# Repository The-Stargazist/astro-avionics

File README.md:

# Astro Avionics: VADA Flight Computer

Dual-computer avionics for amateur and student rockets. The **VADA** board
carries two Raspberry Pi Pico 2 microcontrollers that fly independently:

- **Pico A** watches its own barometer and deploys the parachute.
- **Pico B** reads every sensor and the GPS, sends live LoRa telemetry and
  keeps a detailed log.

Each computer has its own barometer, I2C bus and SD card, so a failure on one
does not take down the other.

> [!WARNING]
> This system controls pyrotechnic charges. The firmware has been rebuilt and
> tested in simulation, but **has not yet flown or been bench-tested on the
> VADA board**. Read [Known issues](#known-issues) and bench-test every pyro
> channel before any flight.

---

## Contents

- [How it works](#how-it-works)
- [Hardware](#hardware)
- [Flight sequence](#flight-sequence)
- [Getting started](#getting-started)
- [Pre-flight checklist](#pre-flight-checklist)
- [Flight data](#flight-data)
- [Repository layout](#repository-layout)
- [Known issues](#known-issues)
- [History](#history)
- [Credits and license](#credits-and-license)

---

## How it works

```mermaid
flowchart LR
    subgraph railA["I2C rail A"]
        IMU["ICM-20649 IMU"]
        MAG["LIS3MDL magnetometer"]
        BMPA["BMP390 A"]
    end
    subgraph railB["I2C rail B"]
        BMPB["BMP390 B"]
    end

    PB["Pico B: sensors, telemetry, logging (FreeRTOS)"]
    PA["Pico A: deployment (dual core)"]

    railA -- "JP1/JP2" --> PB
    railB -- "JP3/JP4" --> PA
    GPS["u-blox M8N GPS"] -- UART --> PB
    PB -- SPI --> LORA["RA-02 LoRa 433 MHz"]
    PB -- SPI --> SDB["SD card B"]
    PA -- SPI --> SDA["SD card A"]
    PA -- fires --> MAIN["MAIN charge"]
    PA -- fires --> BACKUP["BACKUP charge"]
    PB -. "continuity check" .-> MAIN
    PB -. "continuity check" .-> BACKUP
```

| | Pico A: deployment | Pico B: sensors and telemetry |
|---|---|---|
| Barometer | BMP390 "B" (rail B) | BMP390 "A" (rail A) |
| Other sensors | — | ICM-20649 IMU, LIS3MDL magnetometer, GPS |
| Fires pyro charges | **Yes**: MAIN at apogee, BACKUP on overspeed | No (outputs held low) |
| Continuity checks | MAIN, BACKUP, MOTOR, STAGE, check loop | MAIN, BACKUP |
| Logging | SD card A, 50 Hz, `flightNNN.csv` | SD card B, 50 Hz, `telemNNN.csv` |
| Telemetry | — | LoRa, 4 packets/s |
| Runtime | Core 0 flies, core 1 writes the SD card | FreeRTOS tasks |

Both boards run the same flight-phase logic on their own barometer. Pico A
acts on it; Pico B reports it in its log and telemetry. Neither board ever
waits on the SD card or USB while making flight decisions.

## Hardware

The KiCad project for the VADA PCB is in [`vada/`](vada). Everything below
was read from `vada/VADA.kicad_pcb`.

| Part | Function | Connected to |
|------|----------|--------------|
| 2 × Raspberry Pi Pico 2 (RP2350) | Flight computers A and B | — |
| 2 × BMP390 | Barometric altitude | One per I2C rail |
| ICM-20649 | 6-axis IMU, ±30 g / ±2000 °/s | Rail A (Pico B) |
| LIS3MDL | 3-axis magnetometer | Rail A (Pico B) |
| u-blox M8N | GPS | Pico B UART1 (GPIO8/9) |
| Ai-Thinker RA-02 (SX1278) | 433 MHz LoRa radio | Pico B SPI0 |
| 2 × microSD socket | Data logging | One per Pico, SPI0 |
| 4 × CPC1020N solid-state relay | Pyro channels | See below |
| NCP1117-3.3 | 3.3 V regulator from the 5 V input (J1) | — |

**Pyro channels.** Each channel has three lines: TRIG switches battery
power (J7) to the e-match, CONT sends a tiny test current through it, and
SENSE reads it back.

| Channel | Connector | Wired to | Firmware use |
|---------|-----------|----------|--------------|
| MAIN | J2 "Pyro 3" | Both Picos (diode-OR) | Fired by Pico A at apogee |
| BACKUP | J3 "Pyro 4" | Both Picos (diode-OR) | Fired by Pico A if descending too fast |
| MOTOR | J5 "Pyro 1" | Pico A only | Held off, continuity reported |
| STAGE | J6 "Pyro 2" | Pico A only | Held off, continuity reported |

The full pin map for both boards is in
[`firmware/lib/board/VadaPins.h`](firmware/lib/board/VadaPins.h).

## Flight sequence

```mermaid
stateDiagram-v2
    [*] --> GROUND: power on, 1 s ground reference
    GROUND --> FLIGHT: above 200 m AGL for 100 ms
    FLIGHT --> DESCENT: apogee, velocity below 2 m/s for 100 ms, fire MAIN
    DESCENT --> DESCENT: falling faster than 20 m/s for 200 ms, fire BACKUP once
    DESCENT --> LANDED: speed below 2 m/s for 20 s, close log
```

1. **Ground reference.** At power-on each board takes the median of 1 s of
   barometer readings as "pad altitude". All altitudes after that are above
   ground level (AGL).
2. **Filtering.** Raw barometer readings are noisy. A filter smooths them
   into altitude and vertical speed, and throws away single readings that
   are more than 50 m off (a corrupted sensor read).
3. **Launch.** Above 200 m AGL the board switches to FLIGHT. While on the
   ground, Pico A re-checks continuity every second.
4. **Apogee.** When the rocket stops climbing, Pico A fires MAIN for 500 ms.
5. **Overspeed.** If the rocket then falls faster than 20 m/s (main
   failed), Pico A fires BACKUP for 1 s and then MAIN again. This check is
   ignored for the first 2 s after apogee, because the ejection charge
   briefly upsets the barometer.
6. **Landing.** After 20 s with almost no vertical movement, Pico A closes
   its log file.

Every transition has to hold over time, so one bad reading can't trigger it.
All thresholds are in `FlightConfig` in
[`firmware/lib/flight/FlightComputer.h`](firmware/lib/flight/FlightComputer.h).

## Getting started

### Prerequisites

- [PlatformIO](https://platformio.org): either the VS Code extension or the
  command line (`pip install platformio`)
- `gcc` and `g++` on your `PATH` to run the unit tests (on Windows, MSYS2
  or MinGW)

### Build

```bash
git clone https://github.com/The-Stargazist/astro-avionics.git
```

```bash
cd astro-avionics/firmware
```

```bash
pio run
```

The first build downloads the RP2350 toolchain, which takes a few minutes.

### Flash

Connect one Pico at a time over USB. If the upload can't find the board,
unplug it, hold the **BOOTSEL** button and plug it back in.

```bash
pio run -e pico_a -t upload
```

```bash
pio run -e pico_b -t upload
```

Watch the output over USB (Pico A prints its log, Pico B prints a status line
every second):

```bash
pio device monitor
```

### Test

```bash
pio test -e native
```

This runs 22 tests on your computer, no hardware needed:

- simulated flights: normal, failed main, sensor glitches
- GPS sentence parsing
- barometer maths against Bosch's reference values

GitHub Actions runs the tests and both builds on every push.

### Board setup

**Bridge all four solder jumpers JP1, JP2, JP3 and JP4.** They connect
rail A to Pico B and rail B to Pico A. Without them neither board can see its
barometer.

## Pre-flight checklist

1. JP1–JP4 bridged. Two FAT32-formatted microSD cards inserted.
2. Power on **at the launch site**. The pad altitude is measured in the
   first second, so powering on somewhere else shifts every altitude.
3. Check both status LEDs:

   | LED | Meaning |
   |-----|---------|
   | 1 Hz blink | Ready |
   | Solid | MAIN or BACKUP e-match not detected |
   | 5 Hz blink | Sensor, SD card or (Pico B) radio fault |

4. Confirm telemetry is arriving. The `flags` field should show barometer,
   IMU, magnetometer, SD and radio OK, MAIN and BACKUP continuity, and a GPS
   fix (needed for recovery).
5. Check the e-matches are connected before final arming. Pico A re-checks
   continuity every second until launch.

## Flight data

| | Pico A | Pico B |
|---|---|---|
| File | `flightNNN.csv` | `telemNNN.csv` |
| Rate | 50 Hz | 50 Hz |
| Columns | time, pressure, temperature, raw and filtered altitude, velocity, phase | All of Pico A's, plus IMU, magnetometer, GPS and health flags |

A new file is created at every power-on, and data is flushed to the card ten
times a second. Lines starting with `#` are events (launch, apogee, faults);
load the files with `pandas.read_csv(path, comment="#")`.

**Telemetry** (Pico B, LoRa 433 MHz, SF7) is one plain-text line per packet:

```
VADA,time_ms,phase,alt_m,vel_mps,max_alt_m,lat,lon,sats,flags
```

The column definitions and the `flags` bits are in
[`firmware/README.md`](firmware/README.md).

## Repository layout

```
firmware/              current flight software (PlatformIO project)
  src/pico_a/          Pico A application
  src/pico_b/          Pico B application
  lib/board/           pin map for both boards
  lib/flight/          filter, ground reference, flight phases (pure C++, unit-tested)
  lib/gps/             NMEA GPS parser (pure C++, unit-tested)
  lib/sensors/         BMP390, ICM-20649, LIS3MDL drivers
  lib/pyro/            continuity test and firing
  lib/logging/         non-blocking log buffer, SD file naming
  test/                host unit tests
  tools/               MicroPython bring-up script for Pico B
vada/                  VADA PCB: KiCad schematic, layout, 3D model
dosa-2025/             previous flight computer (archived)
```

Technical detail for developers (task layout, file formats, tuning) is in
[`firmware/README.md`](firmware/README.md).

## Known issues

- **Pyro drive current may be too low (hardware).** By the resistor values
  in the PCB file, each solid-state relay gets only about 10–40 µA to switch
  on, but the CPC1020N needs milliamps. If those values are what's fitted,
  the charges may never fire. Bench-test every channel with an e-match
  substitute.
- **No hardware test yet.** The rebuilt firmware compiles and passes its
  simulations, but has not run on a VADA board.
- **Pico A relies on one barometer.** If it fails mid-flight there is no
  timer-based fallback deployment.
- **Only Pico A fires.** The hardware lets Pico B fire MAIN and BACKUP too,
  as a redundant second deployment computer. The firmware doesn't use that.
- **Pico-to-Pico link unused.** The boards are connected by a UART (GPIO0/1)
  that the firmware does not use yet.
- **Barometer labels.** In the schematic the barometers are labelled
  BMP585, but the footprints and firmware are for the BMP390.

## History

- **2025: DOSA** ([`dosa-2025/`](dosa-2025)). Arduino Nano ESP32 for flight
  control plus a Raspberry Pi for logging, camera and backup deployment.
  Archived for reference, not maintained.
- **VADA.** Custom dual-Pico PCB. Separate Pico A and Pico B projects were
  merged into one tested firmware project in `firmware/`.

## Credits and license

This project uses code from Astro Avionics Flight Computer. This fork
(The-Stargazist/astro-avionics) is based on
[YogPanjarale/astro-avionics](https://github.com/YogPanjarale/astro-avionics)
and its contributors.

Released under the MIT License with an attribution requirement: if you use,
modify or distribute this code, credit the original authors. See
[`LICENSE`](LICENSE) for the full terms.

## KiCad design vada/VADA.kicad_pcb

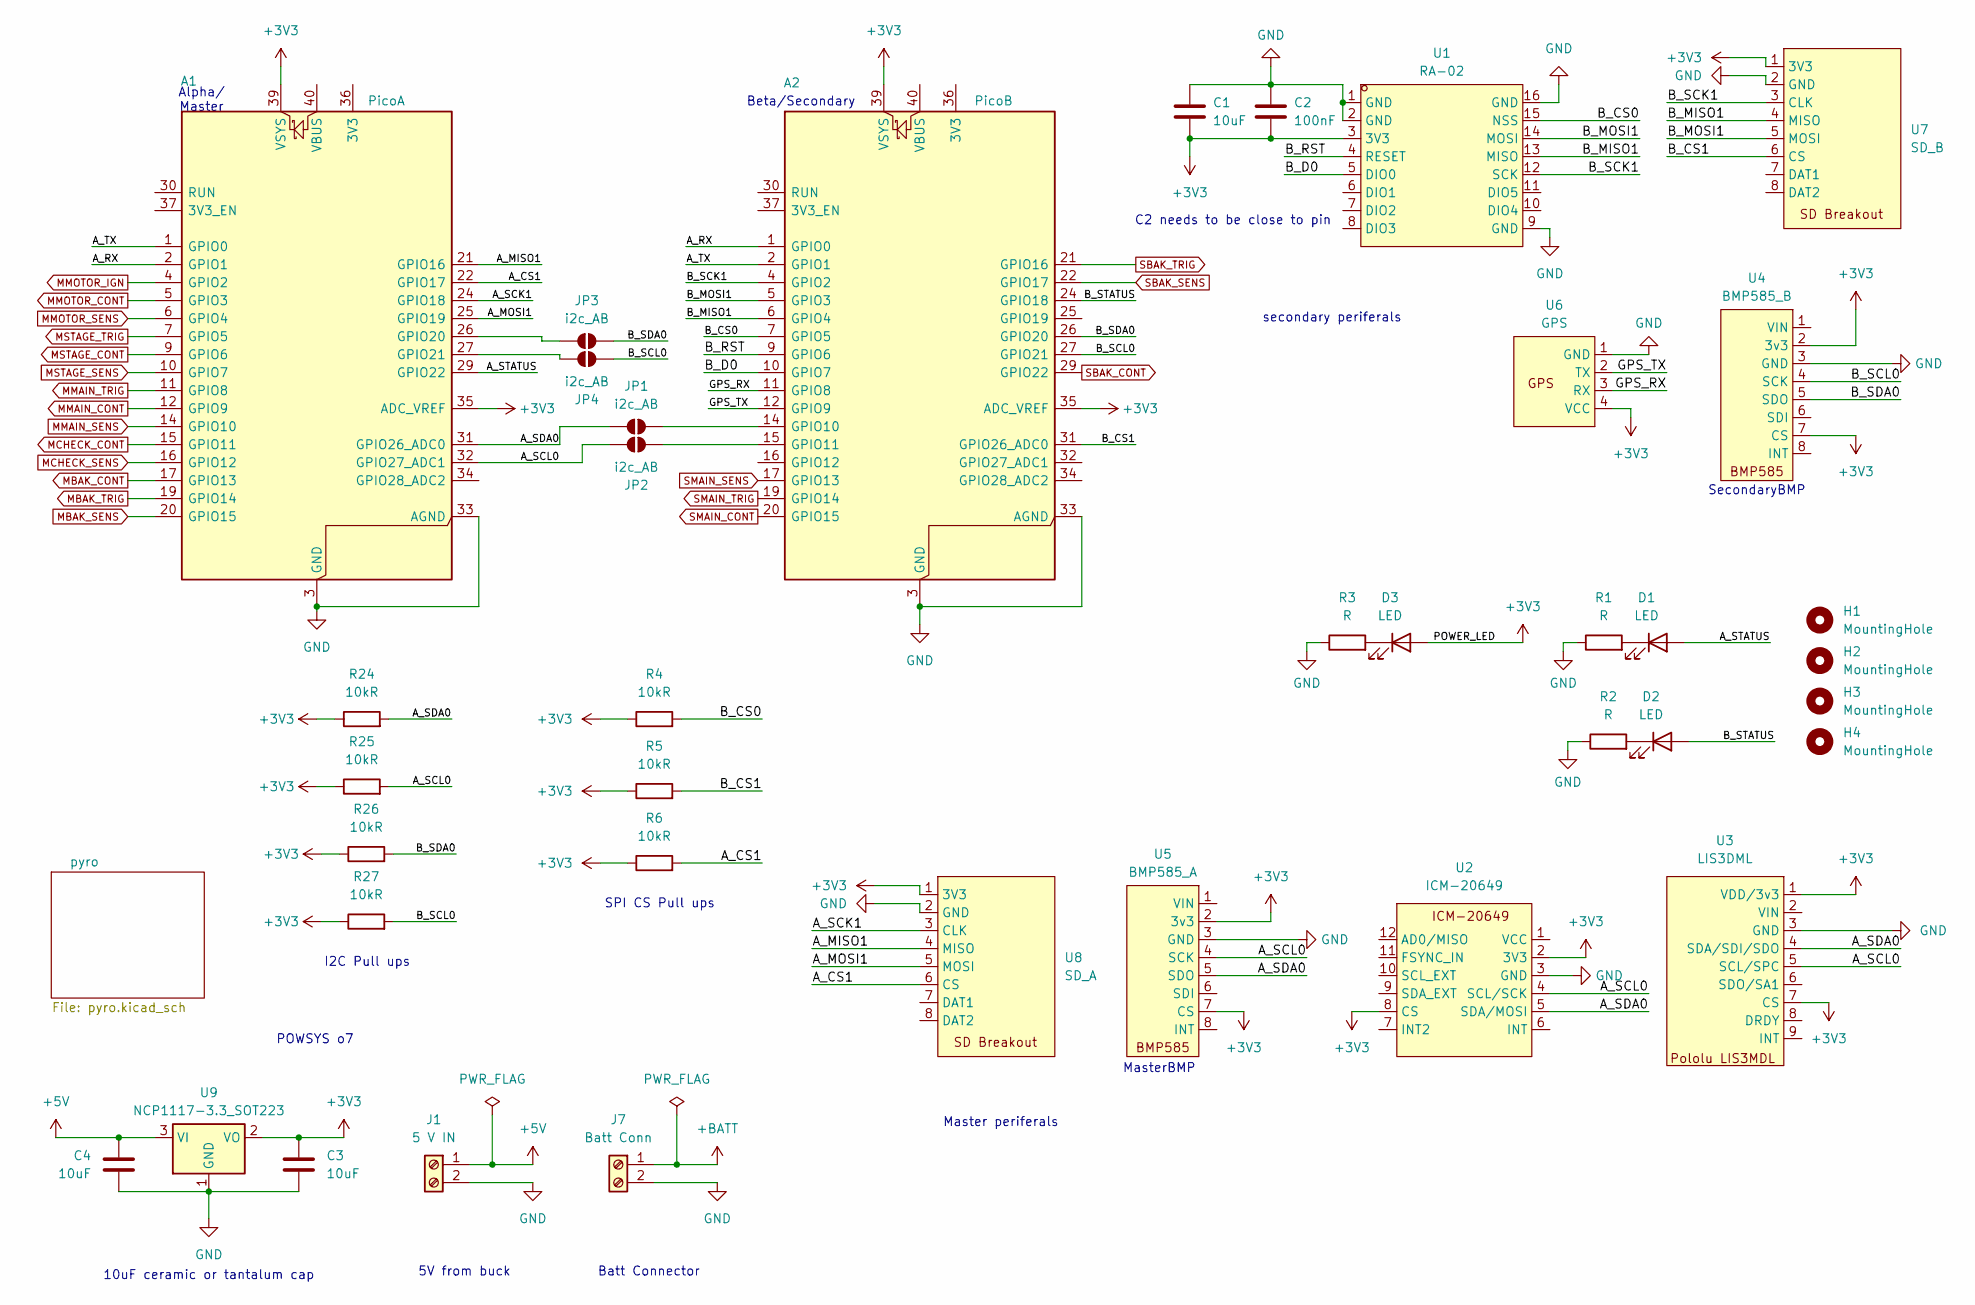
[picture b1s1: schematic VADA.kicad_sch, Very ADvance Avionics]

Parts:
A1: PicoA; RaspberryPi_Pico_Common_THT
A2: PicoB; RaspberryPi_Pico_Common_THT
C1, C3, C4: 10uF; C_1206_3216Metric_Pad1.33x1.80mm_HandSolder
C2: 100nF; C_1206_3216Metric_Pad1.33x1.80mm_HandSolder
D1, D2, D3: LED; LED_D3.0mm
H1, H2, H3, H4: MountingHole; MountingHole_3.2mm_M3
J1: 5 V IN; TerminalBlock_Phoenix_MKDS-1,5-2_1x02_P5.00mm_Horizontal
J7: Batt Conn; TerminalBlock_Phoenix_MKDS-1,5-2_1x02_P5.00mm_Horizontal
JP1, JP2, JP3, JP4: i2c_AB; SolderJumper-2_P1.3mm_Open_Pad1.0x1.5mm
R1, R2, R3: R; R_Axial_DIN0207_L6.3mm_D2.5mm_P7.62mm_Horizontal
R4, R5, R6, R24, R25, R26, R27: 10kR; R_0805_2012Metric_Pad1.20x1.40mm_HandSolder
U1: RA-02; WIRELM-SMD_RA-02-BL; LCSC Part C90039
U2: ICM-20649
U3: LIS3DML; Pololu LIS3DML
U4: BMP585_B; BMP-390L
U5: BMP585_A; BMP-390L
U6: GPS; M8N GPS
U7: SD_B; PinSocket_1x08_P2.54mm_Vertical
U8: SD_A; PinSocket_1x08_P2.54mm_Vertical
U9: NCP1117-3.3_SOT223; SOT-223-3_TabPin2

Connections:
+3V3: A1.35 (ADC_VREF), A1.39 (VSYS), A2.35 (ADC_VREF), A2.39 (VSYS), C1.2, C2.2, C3.1, D3.2 (A), R4.1, R5.1, R6.1, R24.1, R25.1, R26.1, R27.1, U1.3 (3V3), U2.2 (3V3), U2.8 (CS), U3.1 (VDD/3v3), U3.7 (CS), U4.2 (3v3), U4.7 (CS), U5.2 (3v3), U5.7 (CS), U6.4 (VCC), U7.1 (3V3), U8.1 (3V3), U9.2 (VO)
+5V: C4.1, J1.1, U9.3 (VI)
+BATT: J7.1; also elsewhere on the board
/A_CS1: A1.22 (GPIO17), R6.2, U8.6 (CS)
/A_MISO1: A1.21 (GPIO16), U8.4 (MISO)
/A_MOSI1: A1.25 (GPIO19), U8.5 (MOSI)
/A_RX: A1.2 (GPIO1), A2.1 (GPIO0)
/A_SCK1: A1.24 (GPIO18), U8.3 (CLK)
/A_SCL0: A1.32 (GPIO27_ADC1), JP2.1 (A), R25.2, U2.4 (SCL/SCK), U3.5 (SCL/SPC), U5.4 (SCK)
/A_SDA0: A1.31 (GPIO26_ADC0), JP1.1 (A), R24.2, U2.5 (SDA/MOSI), U3.4 (SDA/SDI/SDO), U5.5 (SDO)
/A_STATUS: A1.29 (GPIO22), D1.2 (A)
/A_TX: A1.1 (GPIO0), A2.2 (GPIO1)
/B_CS0: A2.7 (GPIO5), R4.2, U1.15 (NSS)
/B_CS1: A2.31 (GPIO26_ADC0), R5.2, U7.6 (CS)
/B_D0: A2.10 (GPIO7), U1.5 (DIO0)
/B_MISO1: A2.6 (GPIO4), U1.13 (MISO), U7.4 (MISO)
/B_MOSI1: A2.5 (GPIO3), U1.14 (MOSI), U7.5 (MOSI)
/B_RST: A2.9 (GPIO6), U1.4 (RESET)
/B_SCK1: A2.4 (GPIO2), U1.12 (SCK), U7.3 (CLK)
/B_SCL0: A2.27 (GPIO21), JP4.2 (B), R27.2, U4.4 (SCK)
/B_SDA0: A2.26 (GPIO20), JP3.2 (B), R26.2, U4.5 (SDO)
/B_STATUS: A2.24 (GPIO18), D2.2 (A)
/GPS_RX: A2.11 (GPIO8), U6.3 (RX)
/GPS_TX: A2.12 (GPIO9), U6.2 (TX)
GND: A1.3 (GND), A1.8 (GND), A1.13 (GND), A1.18 (GND), A1.23 (GND), A1.28 (GND), A1.33 (AGND), A1.38 (GND), A2.3 (GND), A2.8 (GND), A2.13 (GND), A2.18 (GND), A2.23 (GND), A2.28 (GND), A2.33 (AGND), A2.38 (GND), C1.1, C2.1, C3.2, C4.2, J1.2, J7.2, R1.1, R2.1, R3.1, U1.1 (GND), U1.2 (GND), U1.9 (GND), U1.16 (GND), U2.3 (GND), U3.3 (GND), U4.3 (GND), U5.3 (GND), U6.1 (GND), U7.2 (GND), U8.2 (GND), U9.1 (GND); also elsewhere on the board
MBAK_CONT: A1.17 (GPIO13); also elsewhere on the board
MBAK_SENS: A1.20 (GPIO15), A2.22 (GPIO17); also elsewhere on the board
MBAK_TRIG: A1.19 (GPIO14); also elsewhere on the board
MCHECK_CONT: A1.15 (GPIO11); also elsewhere on the board
MCHECK_SENS: A1.16 (GPIO12); also elsewhere on the board
MMAIN_CONT: A1.12 (GPIO9); also elsewhere on the board
MMAIN_SENS: A1.14 (GPIO10), A2.17 (GPIO13); also elsewhere on the board
MMAIN_TRIG: A1.11 (GPIO8); also elsewhere on the board
MMOTOR_CONT: A1.5 (GPIO3); also elsewhere on the board
MMOTOR_IGN: A1.4 (GPIO2); also elsewhere on the board
MMOTOR_SENS: A1.6 (GPIO4); also elsewhere on the board
MSTAGE_CONT: A1.9 (GPIO6); also elsewhere on the board
MSTAGE_SENS: A1.10 (GPIO7); also elsewhere on the board
MSTAGE_TRIG: A1.7 (GPIO5); also elsewhere on the board
unnamed: A1.26 (GPIO20), JP3.1 (A)
unnamed: A1.27 (GPIO21), JP4.1 (A)
unnamed: A2.14 (GPIO10), JP1.2 (B)
unnamed: A2.15 (GPIO11), JP2.2 (B)
unnamed: D1.1 (K), R1.2
unnamed: D2.1 (K), R2.2
unnamed: D3.1 (K), R3.2
SBAK_CONT: A2.29 (GPIO22); also elsewhere on the board
SBAK_TRIG: A2.21 (GPIO16); also elsewhere on the board
SMAIN_CONT: A2.20 (GPIO15); also elsewhere on the board
SMAIN_TRIG: A2.19 (GPIO14); also elsewhere on the board

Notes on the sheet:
10uF ceramic or tantalum cap
5V from buck
C2 needs to be close to pin
Batt Connector
SPI CS Pull ups
MasterBMP
Alpha/ Master
Master periferals
POWSYS o7
I2C Pull ups
secondary periferals
SecondaryBMP
Beta/Secondary

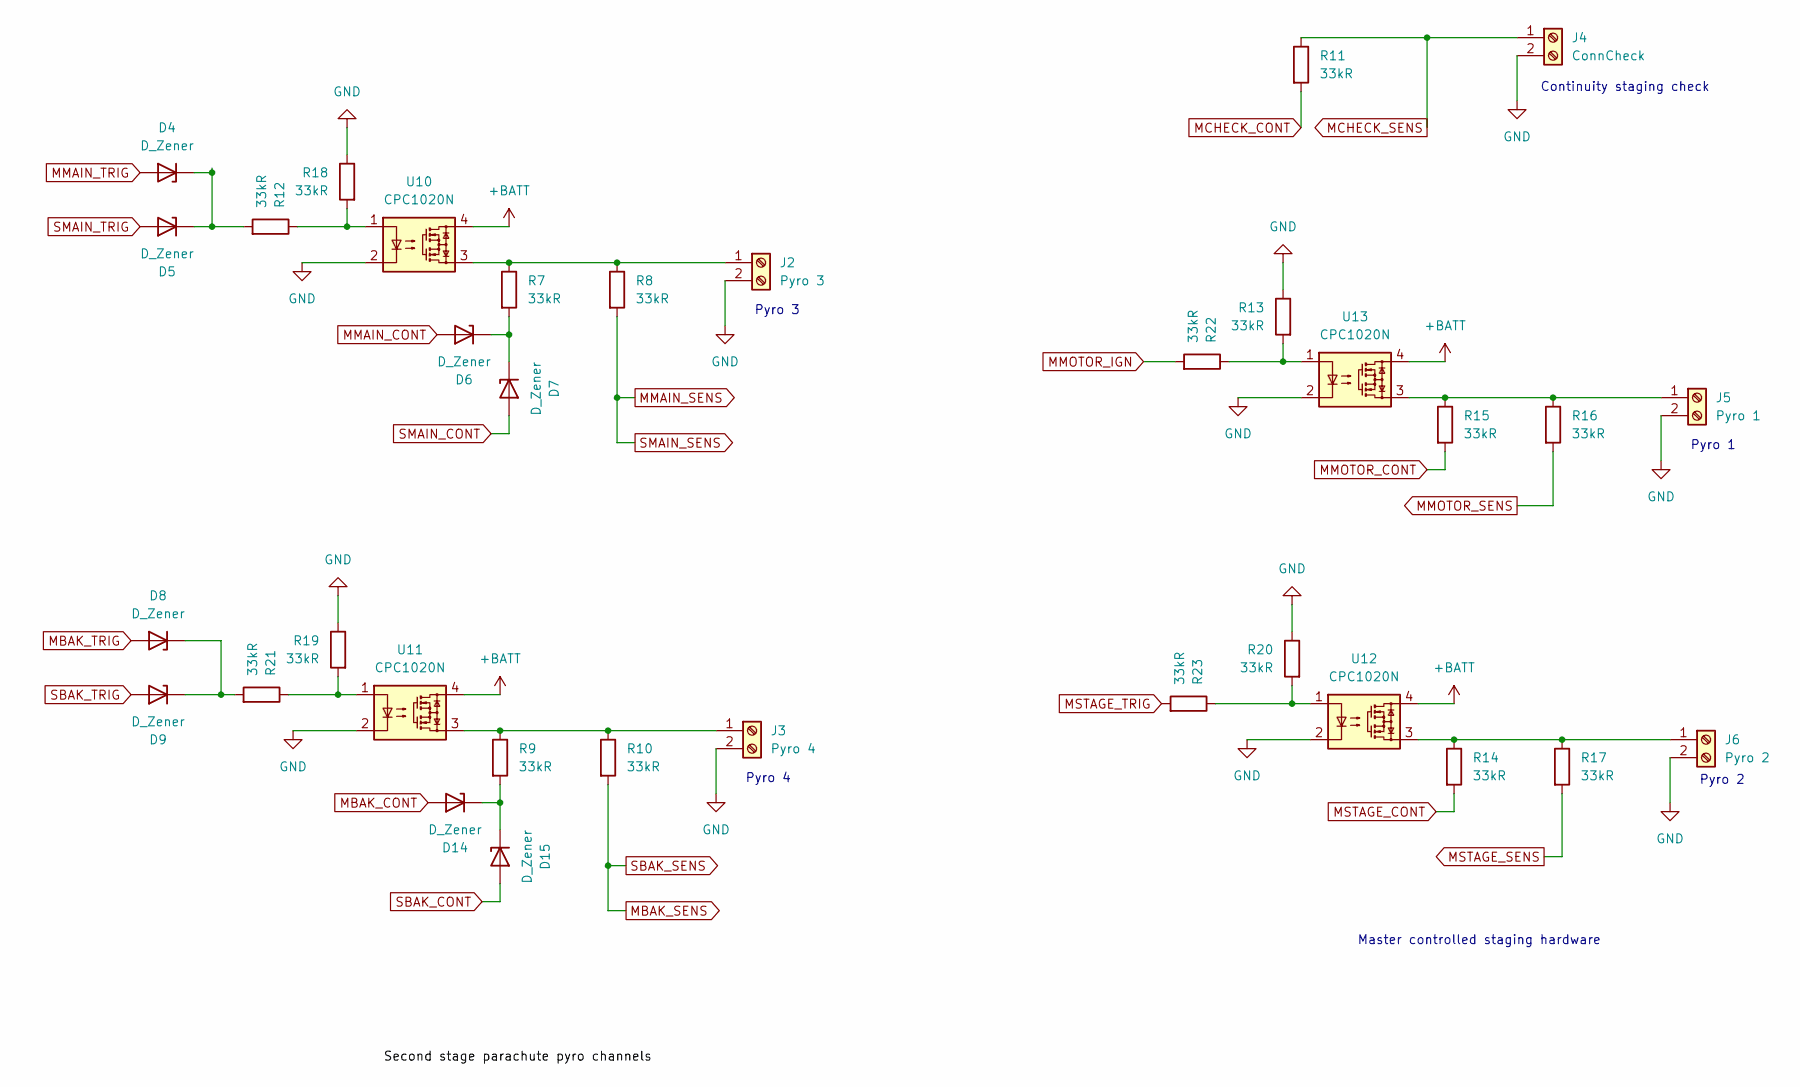
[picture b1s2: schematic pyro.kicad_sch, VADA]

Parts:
D4, D5, D6, D7, D8, D9, D14, D15: D_Zener; D_SOD-123F
J2: Pyro 3; TerminalBlock_Phoenix_MKDS-1,5-2_1x02_P5.00mm_Horizontal
J3: Pyro 4; TerminalBlock_Phoenix_MKDS-1,5-2_1x02_P5.00mm_Horizontal
J4: ConnCheck; TerminalBlock_Phoenix_MKDS-1,5-2_1x02_P5.00mm_Horizontal
J5: Pyro 1; TerminalBlock_Phoenix_MKDS-1,5-2_1x02_P5.00mm_Horizontal
J6: Pyro 2; TerminalBlock_Phoenix_MKDS-1,5-2_1x02_P5.00mm_Horizontal
R7, R8, R9, R10, R11, R12, R13, R14, R15, R16, R17, R18, R19, R20, R21, R22, R23: 33kR; R_0805_2012Metric_Pad1.20x1.40mm_HandSolder
U10, U11, U12, U13: CPC1020N; SOP-4_3.8x4.1mm_P2.54mm

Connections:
+BATT: U10.4, U11.4, U12.4, U13.4; also elsewhere on the board
GND: J2.2, J3.2, J4.2, J5.2, J6.2, R13.1, R18.1, R19.1, R20.1, U10.2, U11.2, U12.2, U13.2; also elsewhere on the board
MBAK_CONT: D14.2 (A); also elsewhere on the board
MBAK_SENS: R10.2; also elsewhere on the board
MBAK_TRIG: D8.2 (A); also elsewhere on the board
MCHECK_CONT: R11.2; also elsewhere on the board
MCHECK_SENS: J4.1, R11.1; also elsewhere on the board
MMAIN_CONT: D6.2 (A); also elsewhere on the board
MMAIN_SENS: R8.2; also elsewhere on the board
MMAIN_TRIG: D4.2 (A); also elsewhere on the board
MMOTOR_CONT: R15.2; also elsewhere on the board
MMOTOR_IGN: R22.2; also elsewhere on the board
MMOTOR_SENS: R16.2; also elsewhere on the board
MSTAGE_CONT: R14.2; also elsewhere on the board
MSTAGE_SENS: R17.2; also elsewhere on the board
MSTAGE_TRIG: R23.2; also elsewhere on the board
unnamed: D4.1 (K), D5.1 (K), R12.2
unnamed: D6.1 (K), D7.1 (K), R7.2
unnamed: D8.1 (K), D9.1 (K), R21.2
unnamed: D14.1 (K), D15.1 (K), R9.2
unnamed: J2.1, R7.1, R8.1, U10.3
unnamed: J3.1, R9.1, R10.1, U11.3
unnamed: J5.1, R15.1, R16.1, U13.3
unnamed: J6.1, R14.1, R17.1, U12.3
unnamed: R12.1, R18.2, U10.1
unnamed: R13.2, R22.1, U13.1
unnamed: R19.2, R21.1, U11.1
unnamed: R20.2, R23.1, U12.1
SBAK_CONT: D15.2 (A); also elsewhere on the board
SBAK_TRIG: D9.2 (A); also elsewhere on the board
SMAIN_CONT: D7.2 (A); also elsewhere on the board
SMAIN_TRIG: D5.2 (A); also elsewhere on the board

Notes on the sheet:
Continuity staging check
Master controlled staging hardware
Pyro 2
Pyro 4
Pyro 3
Pyro 1

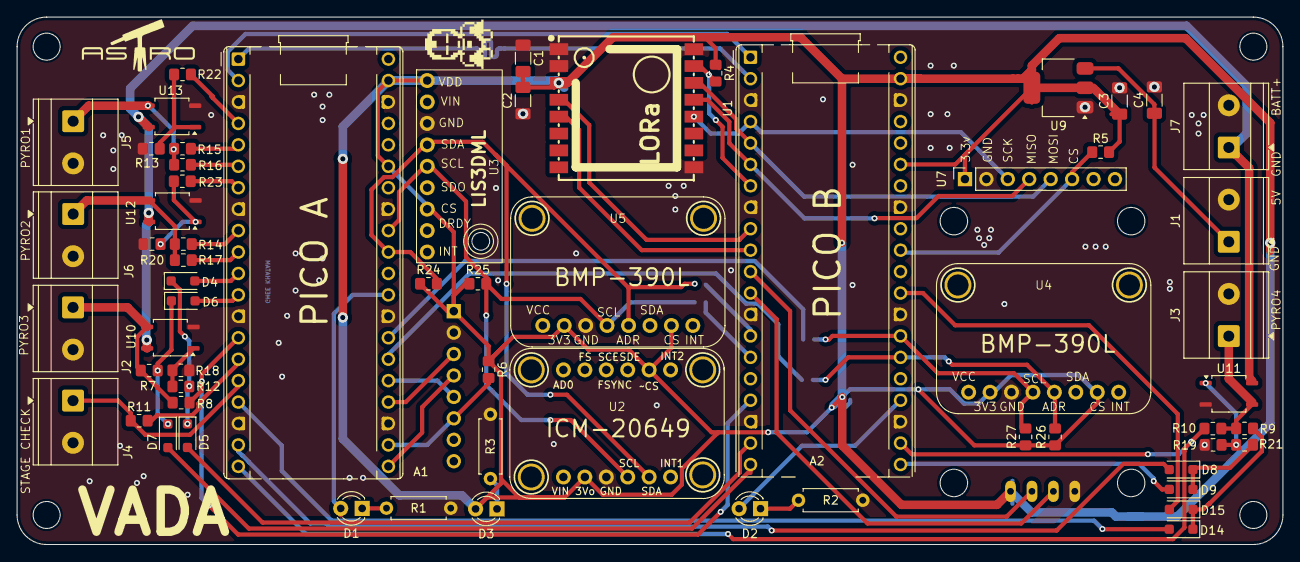
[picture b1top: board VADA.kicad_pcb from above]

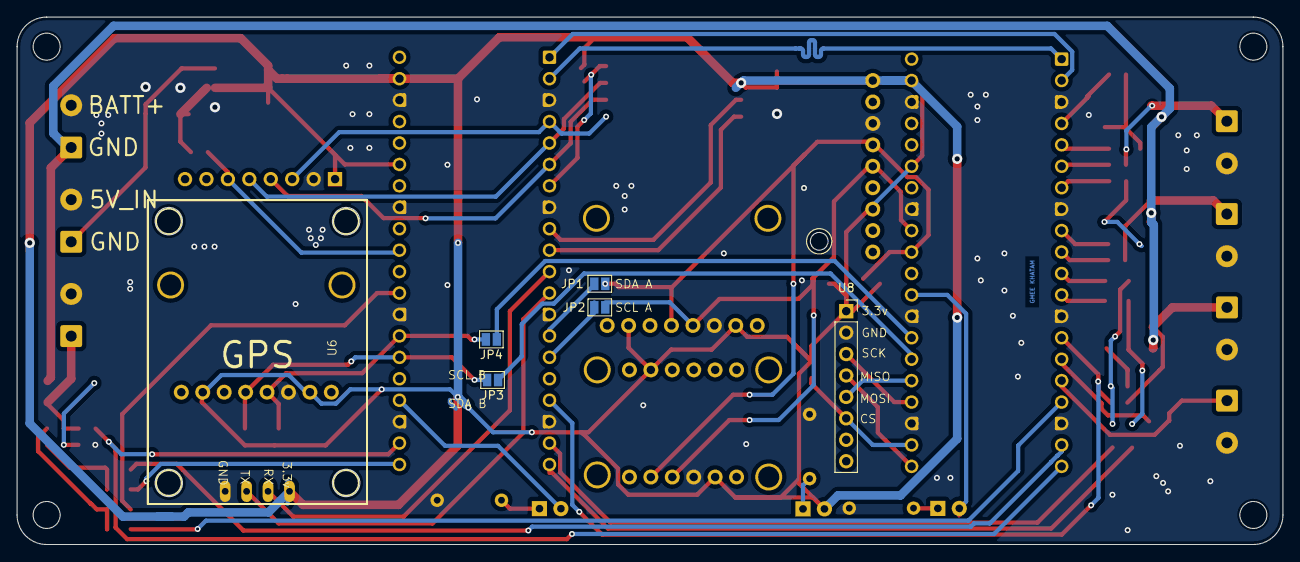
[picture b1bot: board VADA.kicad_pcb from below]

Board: 2 copper layers, 150.0 x 62.5 mm, 72 parts (6 on the bottom side), 62 nets.

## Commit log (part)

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2026-05-24 add pcb 'vada'
